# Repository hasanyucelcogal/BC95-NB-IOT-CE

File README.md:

# BC95-NB-IOT-CE

Quectel BC95 NB IOT IO Module. Assembled fully by hand.

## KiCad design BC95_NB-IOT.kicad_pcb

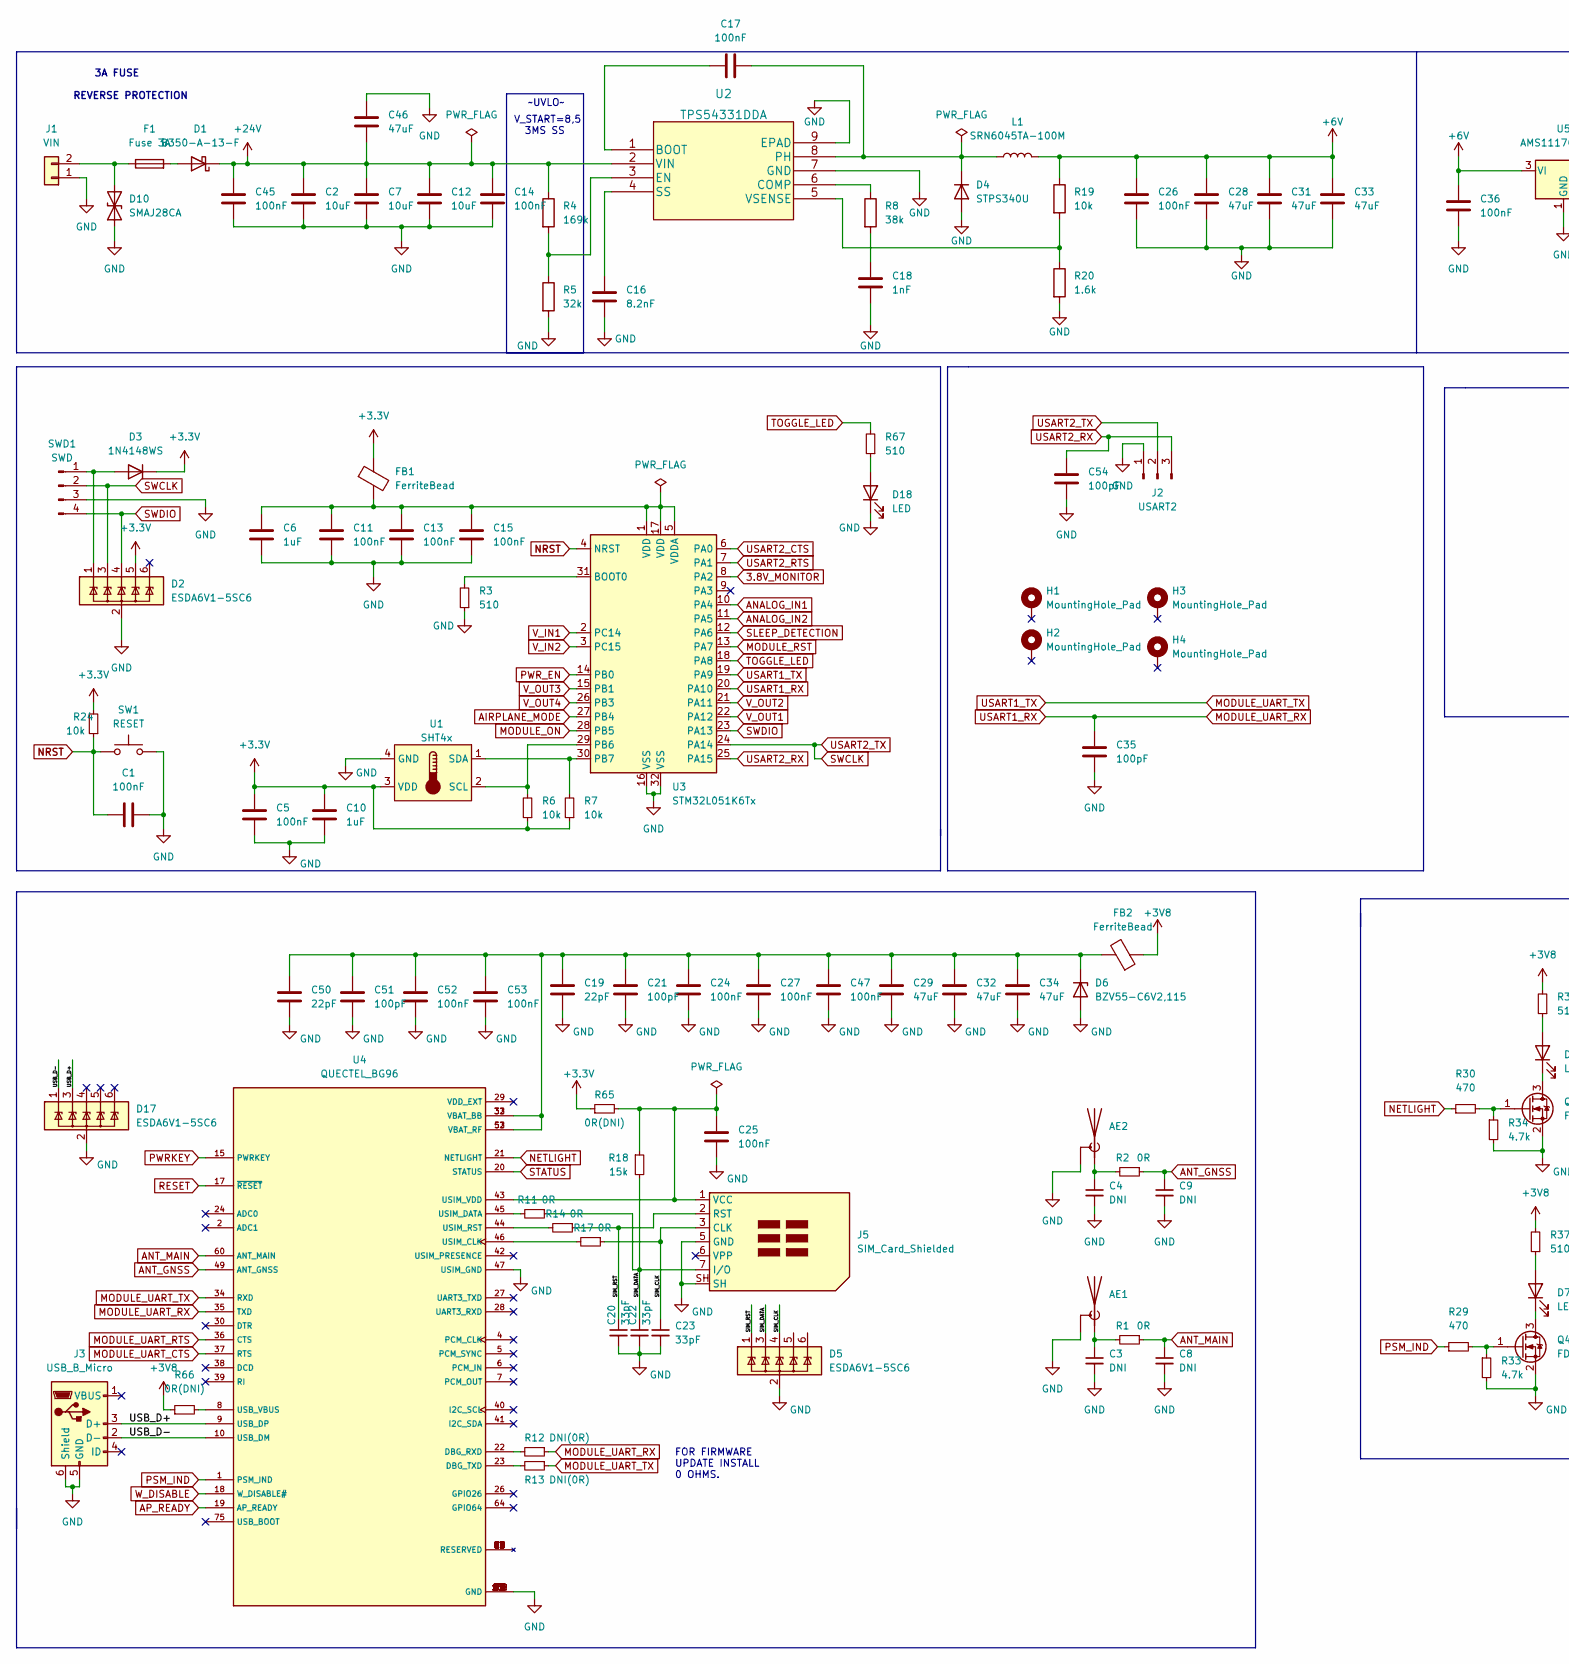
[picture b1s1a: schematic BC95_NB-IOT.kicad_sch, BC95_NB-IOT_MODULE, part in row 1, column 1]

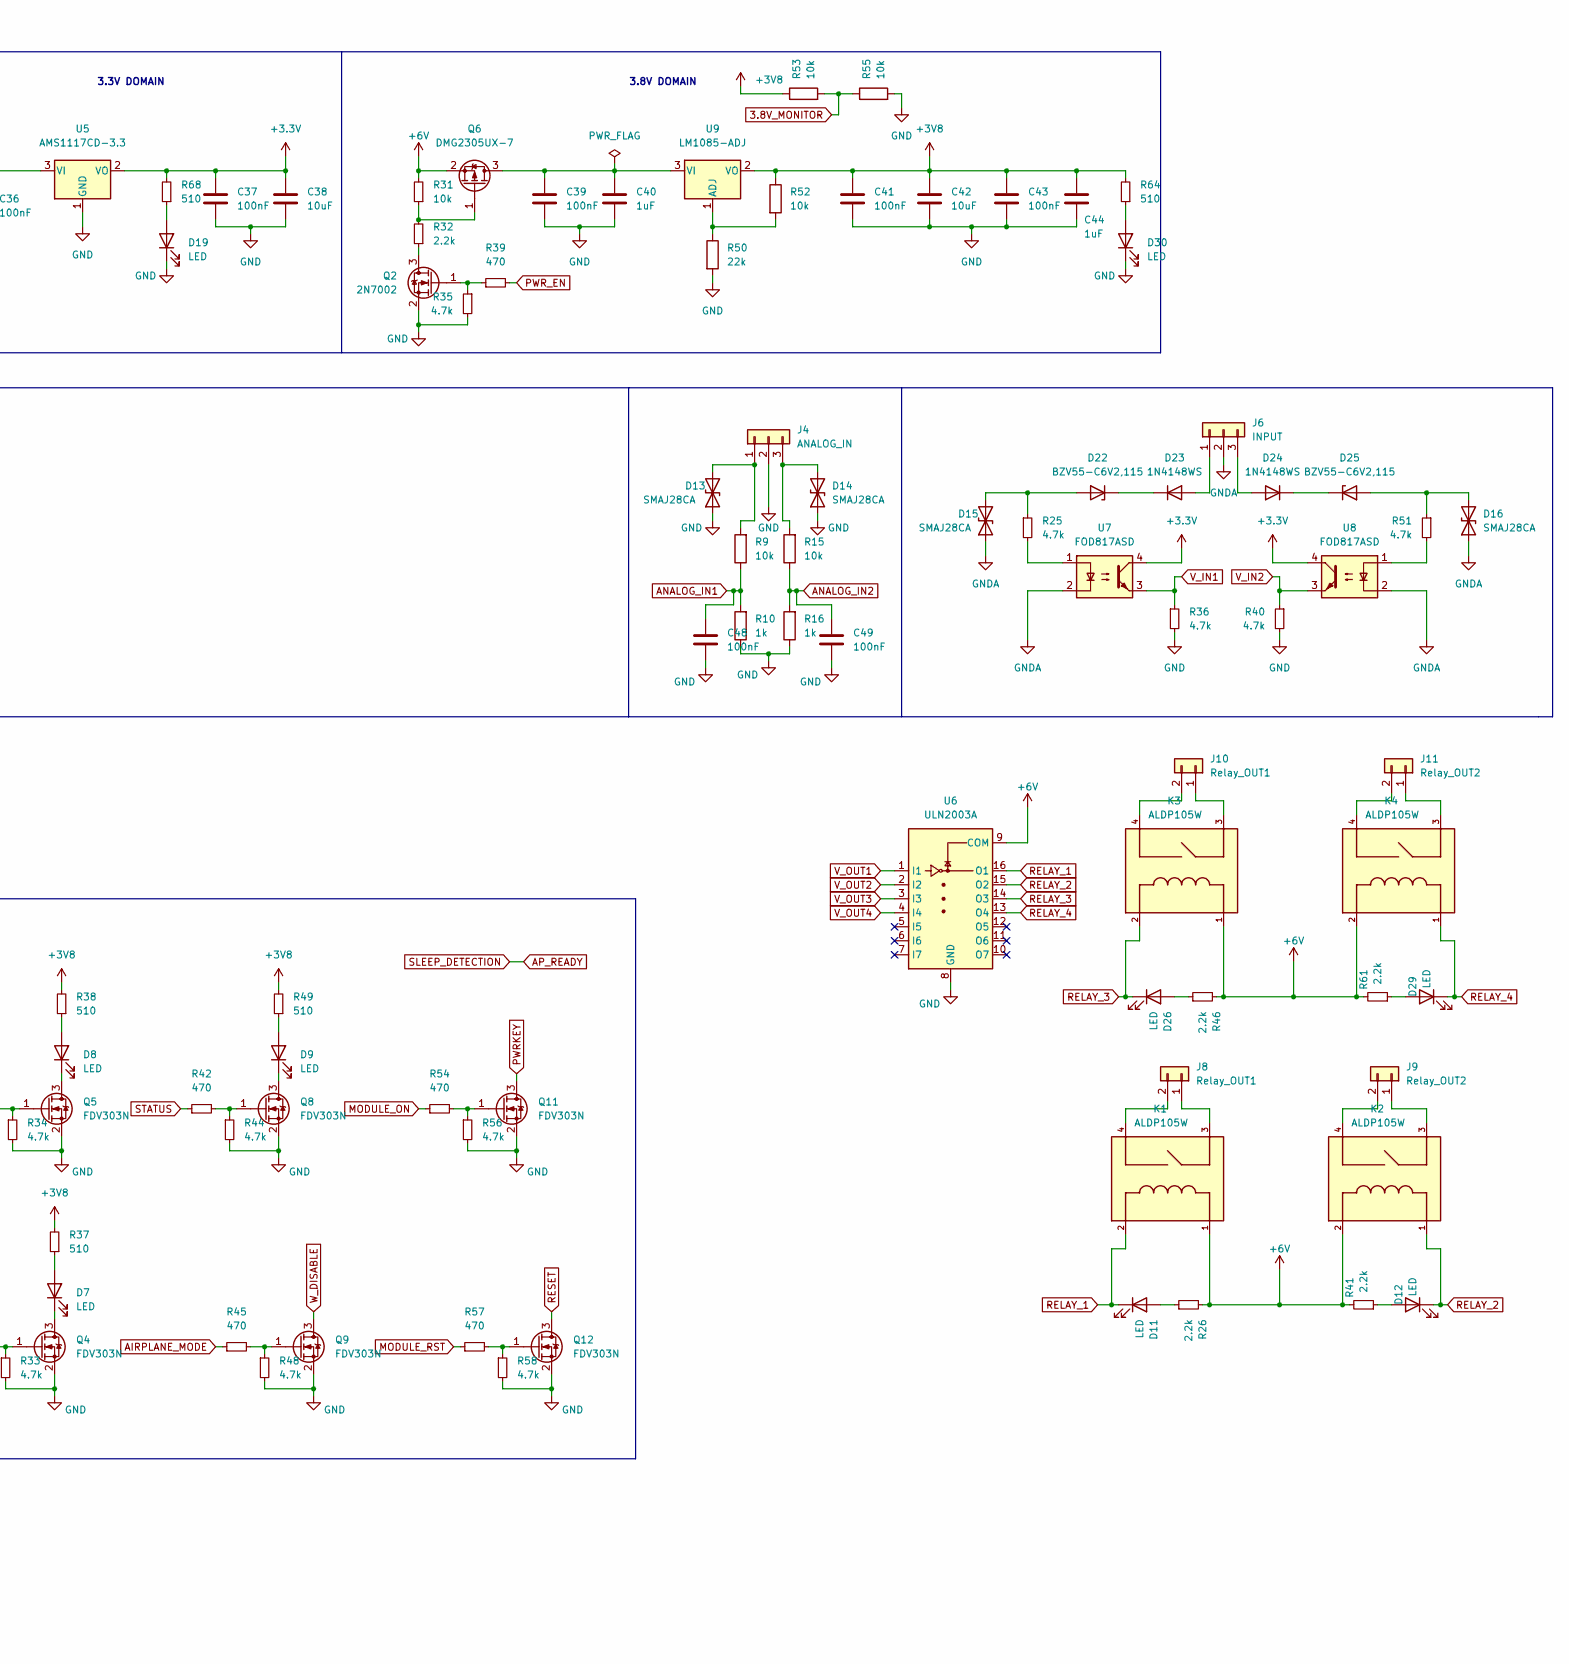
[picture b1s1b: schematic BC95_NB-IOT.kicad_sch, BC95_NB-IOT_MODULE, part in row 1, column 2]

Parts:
AE1, AE2: SMA_Amphenol_132134-10_Vertical
C1, C5, C11, C13, C14, C15, C17, C24, C25, C26, C27, C36, C37, C39, C41, C43, C45, C47, C48, C49, C52, C53: 100nF; C_0603_1608Metric
C2, C7, C12: 10uF; C_1206_3216Metric
C3, C4, C8, C9: DNI; C_0603_1608Metric
C6, C10, C40, C44: 1uF; C_0603_1608Metric
C16: 8.2nF; C_0603_1608Metric
C18: 1nF; C_0603_1608Metric
C19, C50: 22pF; C_0603_1608Metric
C20, C22, C23: 33pF; C_0603_1608Metric
C21, C35, C51, C54: 100pF; C_0603_1608Metric
C28, C29, C31, C32, C33, C34: 47uF; CP_EIA-3528-21_Kemet-B
C38, C42: 10uF; CP_EIA-3528-21_Kemet-B
C46: 47uF; C_1206_3216Metric_Pad1.33x1.80mm_HandSolder
D1: B350-A-13-F; D_SMA
D2, D5, D17: ESDA6V1-5SC6; SOT-23-6
D3, D23, D24: 1N4148WS; D_SOD-323
D4: STPS340U; D_SMB
D6, D22, D25: BZV55-C6V2,115; D_MiniMELF
D7, D8, D9, D11, D12, D18, D19, D26, D29, D30: LED; LED_0603_1608Metric
D10, D13, D14, D15, D16: SMAJ28CA; D_SMA
F1: Fuse 3A; Fuse_Littelfuse-NANO2-451_453
FB1, FB2: FerriteBead; R_0603_1608Metric
H1, H2, H3, H4: MountingHole_Pad; MountingHole_3.2mm_M3_Pad
J1: VIN; TerminalBlock_Phoenix_MKDS-1,5-2-5.08_1x02_P5.08mm_Horizont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
J2: USART2; PinHeader_1x03_P2.54mm_Vertical
J3: USB_B_Micro; USB_Micro-B_Molex_47346-0001
J4: ANALOG_IN; PhoenixContact_MC_1,5_3-G-3.81_1x03_P3.81mm_Horizontal
J5: SIM_Card_Shielded; ATTEND_MICRO_SIM
J6: INPUT; PhoenixContact_MC_1,5_3-G-3.81_1x03_P3.81mm_Horizontal
J8, J10: Relay_OUT1; PhoenixContact_MC_1,5_2-G-5.08_1x02_P5.08mm_Horizontal
J9, J11: Relay_OUT2; PhoenixContact_MC_1,5_2-G-5.08_1x02_P5.08mm_Horizontal
K1, K2, K3, K4: ALDP105W; RELAY_ALDP105W; PARTREV N/A
L1: SRN6045TA-100M; L_Bourns_SRN6045TA
Q2: 2N7002; SOT-23
Q4, Q5, Q8, Q9, Q11, Q12: FDV303N; SOT-23
Q6: DMG2305UX-7; SOT-23
R1, R2, R11, R14, R17: 0R; R_0603_1608Metric
R3, R37, R38, R49, R64, R67, R68: 510; R_0603_1608Metric
R4: 169k; R_0603_1608Metric
R5: 32k; R_0603_1608Metric
R6, R7, R9, R15, R19, R24, R31, R52, R53, R55: 10k; R_0603_1608Metric
R8: 38k; R_0603_1608Metric
R10, R16: 1k; R_0603_1608Metric
R12, R13: DNI(0R); R_0603_1608Metric
R18: 15k; R_0603_1608Metric
R20: 1.6k; R_0603_1608Metric
R25, R33, R34, R35, R36, R40, R44, R48, R51, R56, R58: 4.7k; R_0603_1608Metric
R26, R32, R41, R46, R61: 2.2k; R_0603_1608Metric
R29, R30, R39, R42, R45, R54, R57: 470; R_0603_1608Metric
R50: 22k; R_0603_1608Metric
R65, R66: 0R(DNI); R_0603_1608Metric
SW1: RESET; SW_SPST_B3U-1000P
SWD1: SWD; PinHeader_1x04_P2.54mm_Vertical
U1: SHT4x; SHT4X
U2: TPS54331DDA; TI_SO-PowerPAD-8_ThermalVias
U3: STM32L051K6Tx; LQFP-32_7x7mm_P0.8mm
U4: QUECTEL_BG96; XCVR_BG96
U5: AMS1117CD-3.3; TO-252-3_TabPin2
U6: ULN2003A; SSOP-16_3.9x4.9mm_P0.635mm
U7, U8: FOD817ASD; SMDIP-4_W9.53mm
U9: LM1085-ADJ; TO-263-3_TabPin2

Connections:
3.8V_MONITOR: R53.2, R55.1, U3.8 (PA2)
+3V3: C5.1, C10.1, C37.1, C38.1, D2.5 (IO4), D3.1 (K), FB1.1, R6.1, R7.1, R24.2, R65.1, R68.2, U1.3 (VDD), U5.2 (VO), U7.4, U8.4
+3V8: C41.1, C42.1, C43.1, C44.1, FB2.1, R37.2, R38.2, R49.2, R52.1, R53.1, R64.2, R66.1, U9.2 (VO)
+6V: C26.2, C28.1, C31.1, C33.1, C36.1, K1.1, K2.2, K3.1, K4.2, L1.2, Q6.2 (S), R19.1, R26.2, R31.2, R41.2, R46.2, R61.2, U5.3 (VI), U6.9 (COM)
+24V: C2.1, C7.1, C12.1, C14.2, C45.2, C46.1, D1.1 (K), R4.1, U2.2 (VIN)
/SIM_CLK: C23.1, D5.4 (IO3), J5.3 (CLK), R17.1
/SIM_DATA: C22.1, D5.3 (IO2), J5.7 (I/O), R11.1, R18.2
/SIM_RST: C20.1, D5.1 (IO1), J5.2 (RST), R14.1
/USB_D+: D17.3 (IO2), J3.3 (D+), U4.9 (USB_DP)
/USB_D-: D17.1 (IO1), J3.2 (D-), U4.10 (USB_DM)
AIRPLANE_MODE: R45.1, U3.27 (PB4)
ANALOG_IN1: C48.1, R9.1, R10.2, U3.10 (PA4)
ANALOG_IN2: C49.1, R15.1, R16.2, U3.11 (PA5)
ANT_GNSS: C9.1, R2.1, U4.49 (ANT_GNSS)
ANT_MAIN: C8.1, R1.1, U4.60 (ANT_MAIN)
AP_READY: U3.12 (PA6), U4.19 (AP_READY)
GND: AE1.2 (Shield), AE2.2 (Shield), C1.2, C2.2, C3.2, C4.2, C5.2, C6.2, C7.2, C8.2, C9.2, C10.2, C11.2, C12.2, C13.2, C14.1, C15.2, C16.1, C18.1, C19.2, C20.2, C21.2, C22.2, C23.2, C24.2, C25.2, C26.1, C27.2, C28.2, C29.2, C31.2, C32.2, C33.2, C34.2, C35.2, C36.2, C37.2, C38.2, C39.2, C40.2, C41.2, C42.2, C43.2, C44.2, C45.1, C46.2, C47.2, C48.2, C49.2, C50.2, C51.2, C52.2, C53.2, C54.2, D2.2 (GND), D4.2 (A), D5.2 (GND), D6.2 (A), D10.1 (A1), D13.1 (A1), D14.1 (A1), D17.2 (GND), D18.1 (K), D19.1 (K), D30.1 (K), J1.1, J2.1, J3.5 (GND), J3.6 (Shield), J4.2, J5.5 (GND), J5.SH, Q2.2 (S), Q4.2 (S), Q5.2 (S), Q8.2 (S), Q9.2 (S), Q11.2 (S), Q12.2 (S), R3.1, R5.2, R10.1, R16.1, R20.2, R33.2, R34.2, R35.2, R36.2, R40.2, R44.2, R48.2, R50.2, R55.2, R56.2, R58.2, SW1.2, SWD1.3, U1.4 (GND), U2.7 (GND), U2.9 (EPAD), U3.16 (VSS), U3.32 (VSS), U4.3 (GND), U4.31 (GND), U4.47 (USIM_GND), U4.48 (GND), U4.50 (GND), U4.54 (GND), U4.55 (GND), U4.58 (GND), U4.59 (GND), U4.61 (GND), U4.62 (GND), U4.67 (GND), U4.68 (GND), U4.69 (GND), U4.70 (GND), U4.71 (GND), U4.72 (GND), U4.73 (GND), U4.74 (GND), U4.79 (GND), U4.80 (GND), U4.81 (GND), U4.82 (GND), U4.89 (GND), U4.90 (GND), U4.91 (GND), U4.100 (GND), U4.101 (GND), U4.102 (GND), U5.1 (GND), U6.8 (GND)
GNDA: D15.1 (A1), D16.1 (A1), J6.2, U7.2, U8.2
MODULE_ON: R54.1, U3.28 (PB5)
MODULE_RST: R57.1, U3.13 (PA7)
MODULE_UART_CTS: U4.37 (RTS)
MODULE_UART_RTS: U4.36 (CTS)
MODULE_UART_RX: C35.1, R12.1, U3.20 (PA10), U4.35 (TXD)
MODULE_UART_TX: R13.1, U3.19 (PA9), U4.34 (RXD)
NETLIGHT: R30.1, U4.21 (NETLIGHT)
NRST: C1.1, R24.1, SW1.1, U3.4 (NRST)
unnamed: AE1.1 (A), C3.1, R1.2
unnamed: AE2.1 (A), C4.1, R2.2
unnamed: C6.1, C11.1, C13.1, C15.1, FB1.2, U3.1 (VDD), U3.5 (VDDA), U3.17 (VDD)
unnamed: C16.2, U2.4 (SS)
unnamed: C17.1, U2.1 (BOOT)
unnamed: C17.2, D4.1 (K), L1.1, U2.8 (PH)
unnamed: C18.2, R8.2
unnamed: C19.1, C21.1, C24.1, C27.1, C29.1, C32.1, C34.1, C47.1, C50.1, C51.1, C52.1, C53.1, D6.1 (K), FB2.2, U4.32 (VBAT_BB), U4.33 (VBAT_BB), U4.52 (VBAT_RF), U4.53 (VBAT_RF)
unnamed: C25.1, J5.1 (VCC), R18.1, R65.2, U4.43 (USIM_VDD)
unnamed: C39.1, C40.1, Q6.3 (D), U9.3 (VI)
unnamed: D1.2 (A), F1.2
unnamed: D2.1 (IO1), D3.2 (A), SWD1.1
unnamed: D7.1 (K), Q4.3 (D)
unnamed: D7.2 (A), R37.1
unnamed: D8.1 (K), Q5.3 (D)
unnamed: D8.2 (A), R38.1
unnamed: D9.1 (K), Q8.3 (D)
unnamed: D9.2 (A), R49.1
unnamed: D10.2 (A2), F1.1, J1.2
unnamed: D11.2 (A), R26.1
unnamed: D12.2 (A), R41.1
unnamed: D13.2 (A2), J4.1, R9.2
unnamed: D14.2 (A2), J4.3, R15.2
unnamed: D15.2 (A2), D22.2 (A), R25.1
unnamed: D16.2 (A2), D25.2 (A), R51.1
unnamed: D18.2 (A), R67.1
unnamed: D19.2 (A), R68.1
unnamed: D22.1 (K), D23.1 (K)
unnamed: D23.2 (A), J6.1
unnamed: D24.1 (K), D25.1 (K)
unnamed: D24.2 (A), J6.3
unnamed: D26.2 (A), R46.1
unnamed: D29.2 (A), R61.1
unnamed: D30.2 (A), R64.1
unnamed: J8.1, K1.3
unnamed: J8.2, K1.4
unnamed: J9.1, K2.3
unnamed: J9.2, K2.4
unnamed: J10.1, K3.3
unnamed: J10.2, K3.4
unnamed: J11.1, K4.3
unnamed: J11.2, K4.4
unnamed: Q2.1 (G), R35.1, R39.1
unnamed: Q2.3 (D), R32.1
unnamed: Q4.1 (G), R29.2, R33.1
unnamed: Q5.1 (G), R30.2, R34.1
unnamed: Q6.1 (G), R31.1, R32.2
unnamed: Q8.1 (G), R42.2, R44.1
unnamed: Q9.1 (G), R45.2, R48.1
unnamed: Q11.1 (G), R54.2, R56.1
unnamed: Q12.1 (G), R57.2, R58.1
unnamed: R3.2, U3.31 (BOOT0)
unnamed: R4.2, R5.1, U2.3 (EN)
unnamed: R6.2, U1.2 (SCL), U3.29 (PB6)
unnamed: R7.2, U1.1 (SDA), U3.30 (PB7)
unnamed: R8.1, U2.6 (COMP)
unnamed: R11.2, U4.45 (USIM_DATA)
unnamed: R12.2, U4.22 (DBG_RXD)
unnamed: R13.2, U4.23 (DBG_TXD)
unnamed: R14.2, U4.44 (USIM_RST)
unnamed: R17.2, U4.46 (USIM_CLK)
unnamed: R19.2, R20.1, U2.5 (VSENSE)
unnamed: R25.2, U7.1
unnamed: R50.1, R52.2, U9.1 (ADJ)
unnamed: R51.2, U8.1
unnamed: R66.2, U4.8 (USB_VBUS)
PSM_IND: R29.1, U4.1 (PSM_IND)
PWRKEY: Q11.3 (D), U4.15 (PWRKEY)
PWR_EN: R39.2, U3.14 (PB0)
RELAY_1: D11.1 (K), K1.2, U6.16 (O1)
RELAY_2: D12.1 (K), K2.1, U6.15 (O2)
RELAY_3: D26.1 (K), K3.2, U6.14 (O3)
RELAY_4: D29.1 (K), K4.1, U6.13 (O4)
RESET: Q12.3 (D), U4.17 (~RESET)
STATUS: R42.1, U4.20 (STATUS)
SWCLK: D2.3 (IO2), J2.2, SWD1.2, U3.24 (PA14)
SWDIO: D2.4 (IO3), SWD1.4, U3.23 (PA13)
TOGGLE_LED: R67.2, U3.18 (PA8)
USART2_CTS: U3.6 (PA0)
USART2_RTS: U3.7 (PA1)
USART2_RX: C54.1, J2.3, U3.25 (PA15)
V_IN1: R36.1, U3.2 (PC14), U7.3
V_IN2: R40.1, U3.3 (PC15), U8.3
V_OUT1: U3.22 (PA12), U6.1 (I1)
V_OUT2: U3.21 (PA11), U6.2 (I2)
V_OUT3: U3.15 (PB1), U6.3 (I3)
V_OUT4: U3.26 (PB3), U6.4 (I4)
W_DISABLE: Q9.3 (D), U4.18 (W_DISABLE#)

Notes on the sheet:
FOR FIRMWARE UPDATE INSTALL 0 OHMS.
V_START=8,5 3MS SS
~UVLO~
3.3V DOMAIN
3A FUSE REVERSE PROTECTION
3.8V DOMAIN

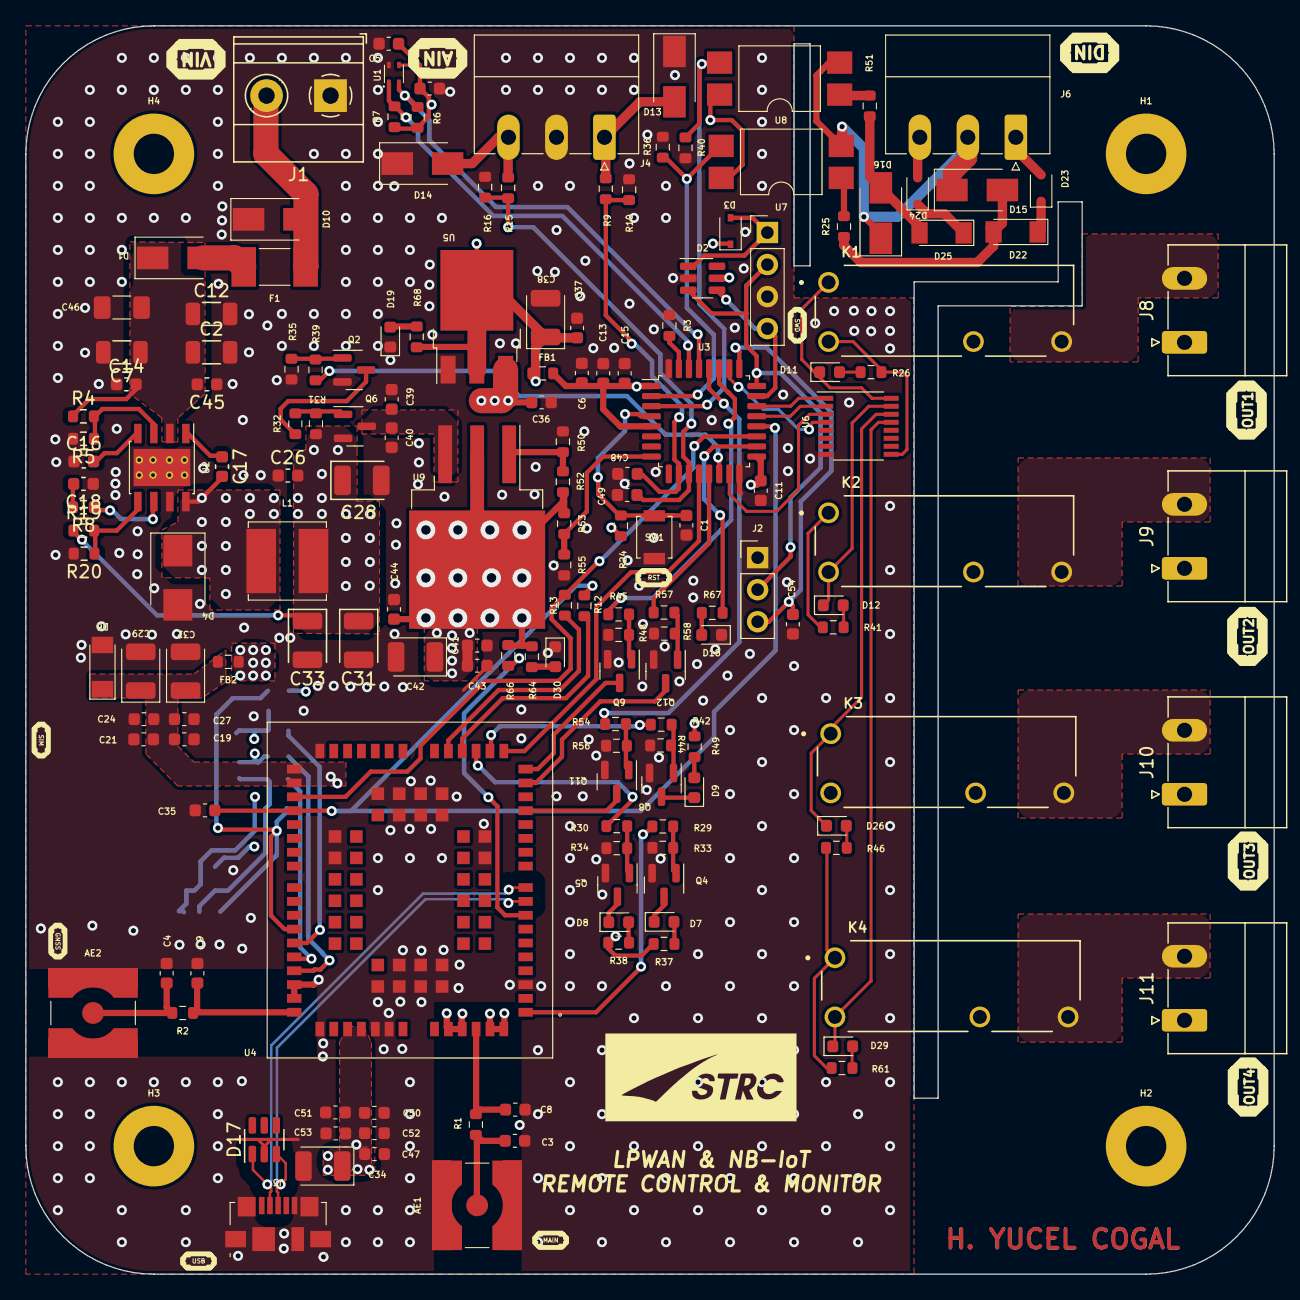
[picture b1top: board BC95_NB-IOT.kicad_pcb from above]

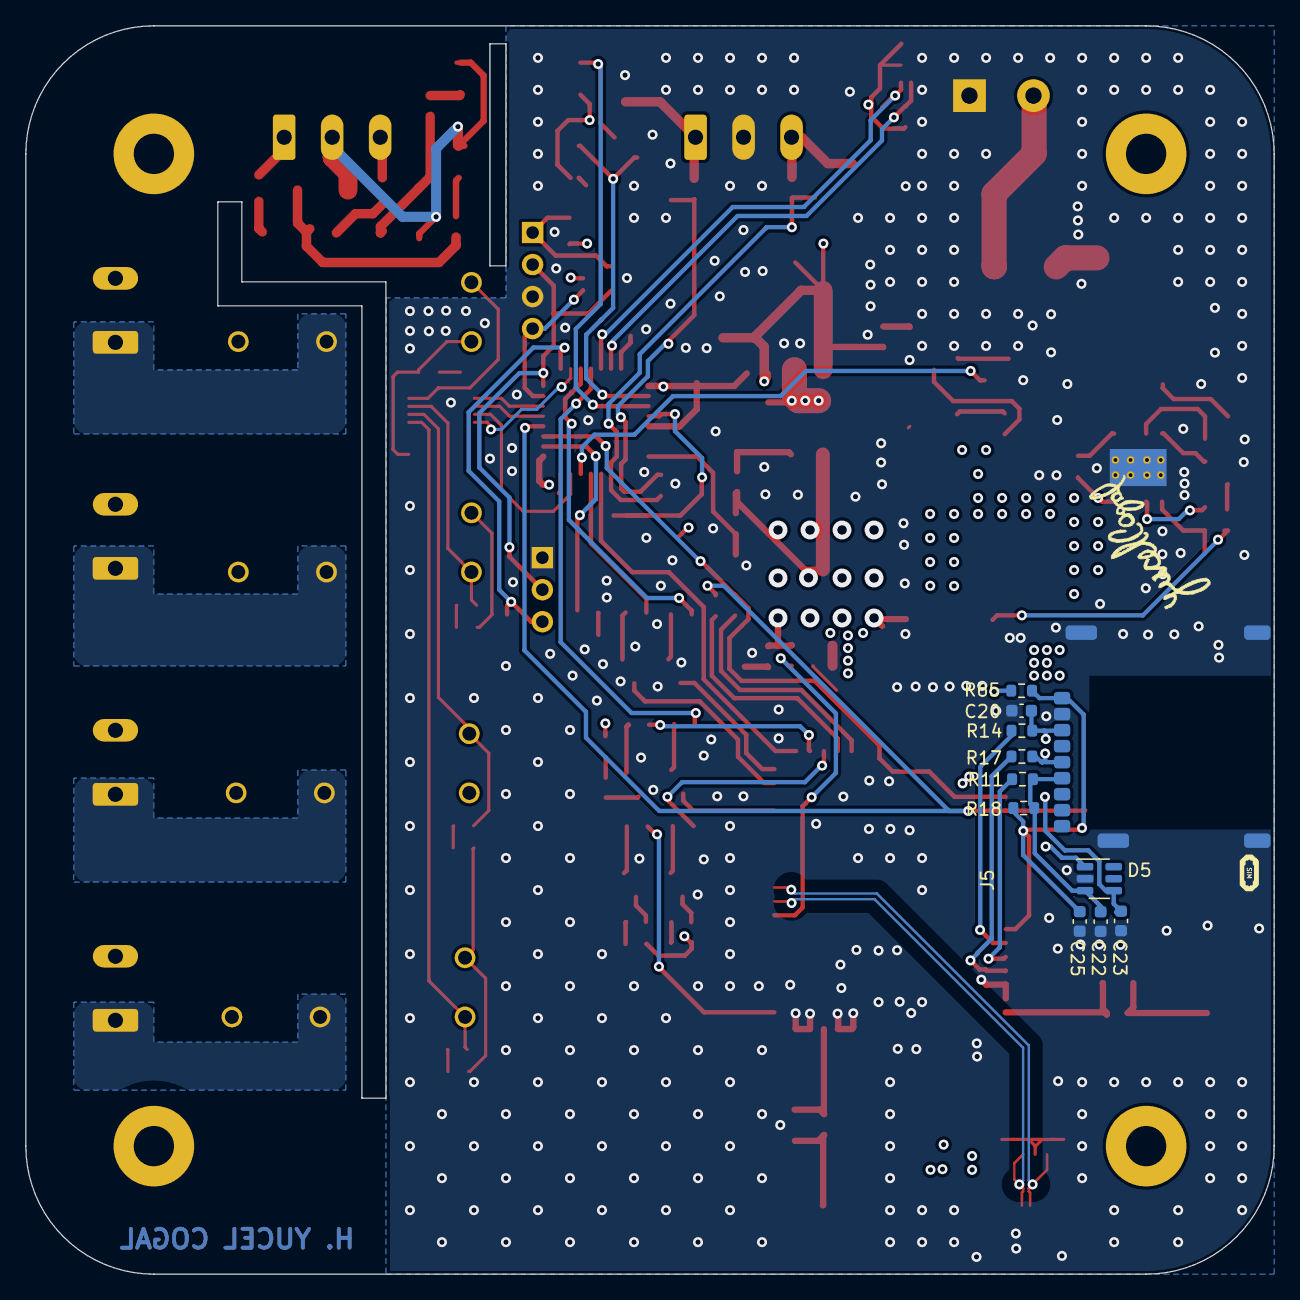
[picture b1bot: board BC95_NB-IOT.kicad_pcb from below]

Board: 4 copper layers, 99.1 x 99.1 mm, 179 parts (11 on the bottom side), 110 nets.

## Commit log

2023-02-16 bom update
2023-02-16 gerber generating
2023-03-18 Backlink to CADLAB.io has been added.
